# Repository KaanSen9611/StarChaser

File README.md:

# StarChaser
A multi color LED Chaser shaped like a star.

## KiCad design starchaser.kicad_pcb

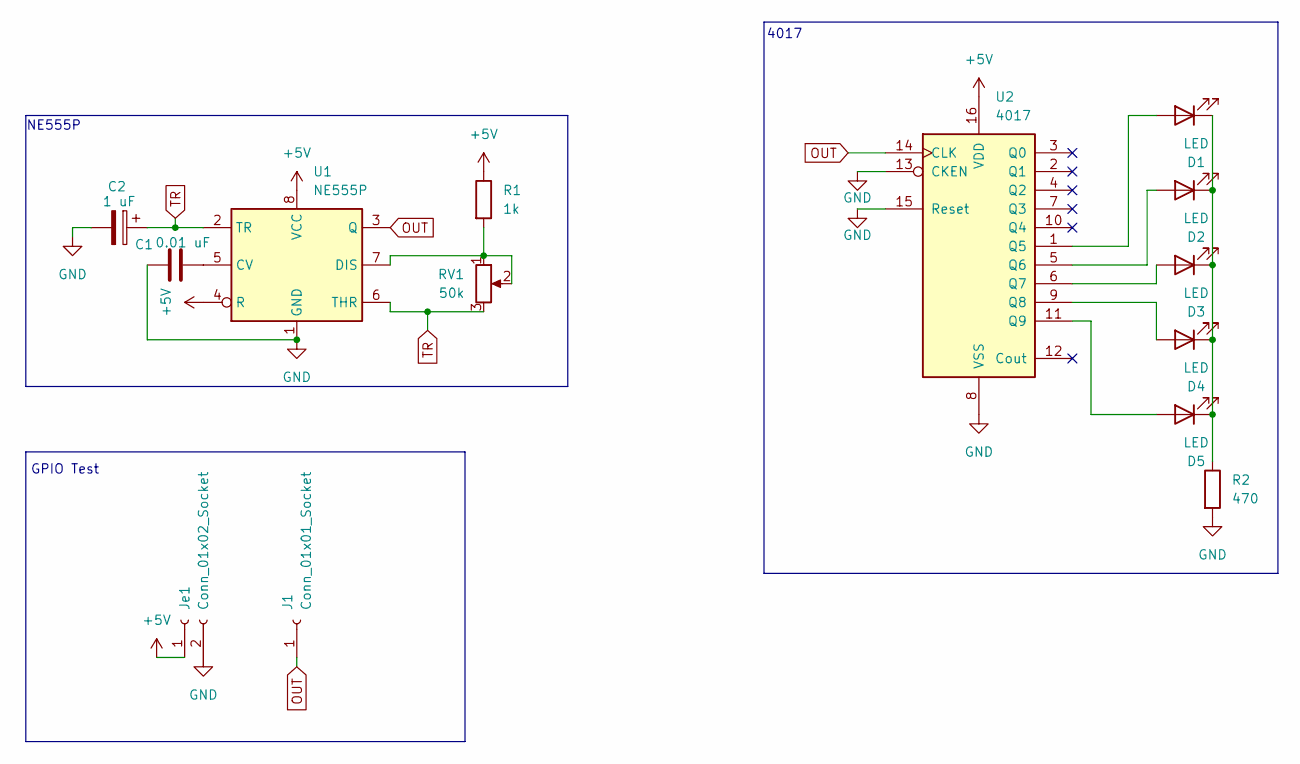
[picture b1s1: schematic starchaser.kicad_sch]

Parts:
C1: 0.01 uF; C_Disc_D7.5mm_W2.5mm_P5.00mm
C2: 1 uF; CP_Radial_D5.0mm_P2.00mm
D1, D2, D3, D4, D5: LED; LED_D3.0mm
J1: Conn_01x01_Socket; PinHeader_1x01_P2.54mm_Vertical
Je1: Conn_01x02_Socket; PinHeader_1x02_P2.54mm_Vertical
R1: 1k; R_Axial_DIN0207_L6.3mm_D2.5mm_P2.54mm_Vertical
R2: 470; R_Axial_DIN0207_L6.3mm_D2.5mm_P2.54mm_Vertical
RV1: 50k; Potentiometer_Vishay_T93YA_Vertical
U1: NE555P; DIP-8_W7.62mm
U2: 4017; N16

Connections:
+5V: Je1.1, R1.1, U1.4 (R), U1.8 (VCC), U2.16 (VDD)
GND: C1.1, C2.2, Je1.2, R2.2, U1.1 (GND), U2.8 (VSS), U2.13 (CKEN), U2.15 (Reset)
unnamed: D1.2 (A), U2.1 (Q5)
unnamed: D1.1 (K), D2.1 (K), D3.1 (K), D4.1 (K), D5.1 (K), R2.1
unnamed: D2.2 (A), U2.5 (Q6)
unnamed: D3.2 (A), U2.6 (Q7)
unnamed: D4.2 (A), U2.9 (Q8)
unnamed: D5.2 (A), U2.11 (Q9)
unnamed: C1.2, U1.5 (CV)
unnamed: R1.2, RV1.1, RV1.2, U1.7 (DIS)
OUT: J1.1, U1.3 (Q), U2.14 (CLK)
TR: C2.1, RV1.3, U1.2 (TR), U1.6 (THR)

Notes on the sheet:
GPIO Test
4017
NE555P

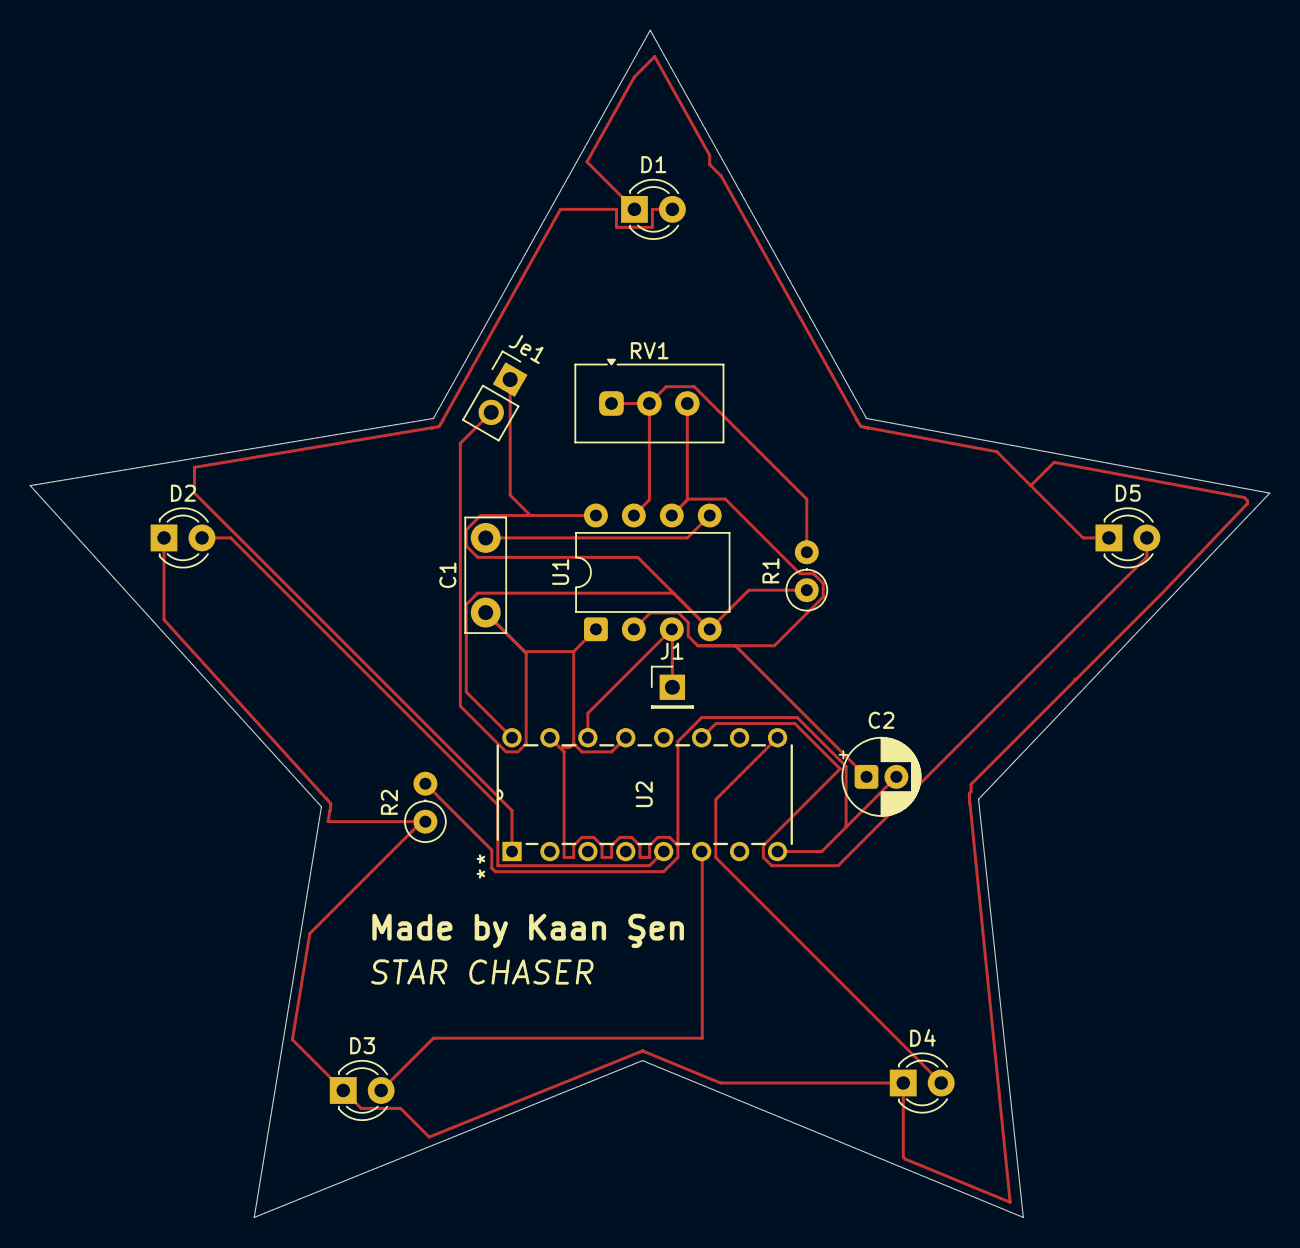
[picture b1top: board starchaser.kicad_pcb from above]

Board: 2 copper layers, 83.0 x 79.5 mm, 14 parts (0 on the bottom side), 12 nets.
